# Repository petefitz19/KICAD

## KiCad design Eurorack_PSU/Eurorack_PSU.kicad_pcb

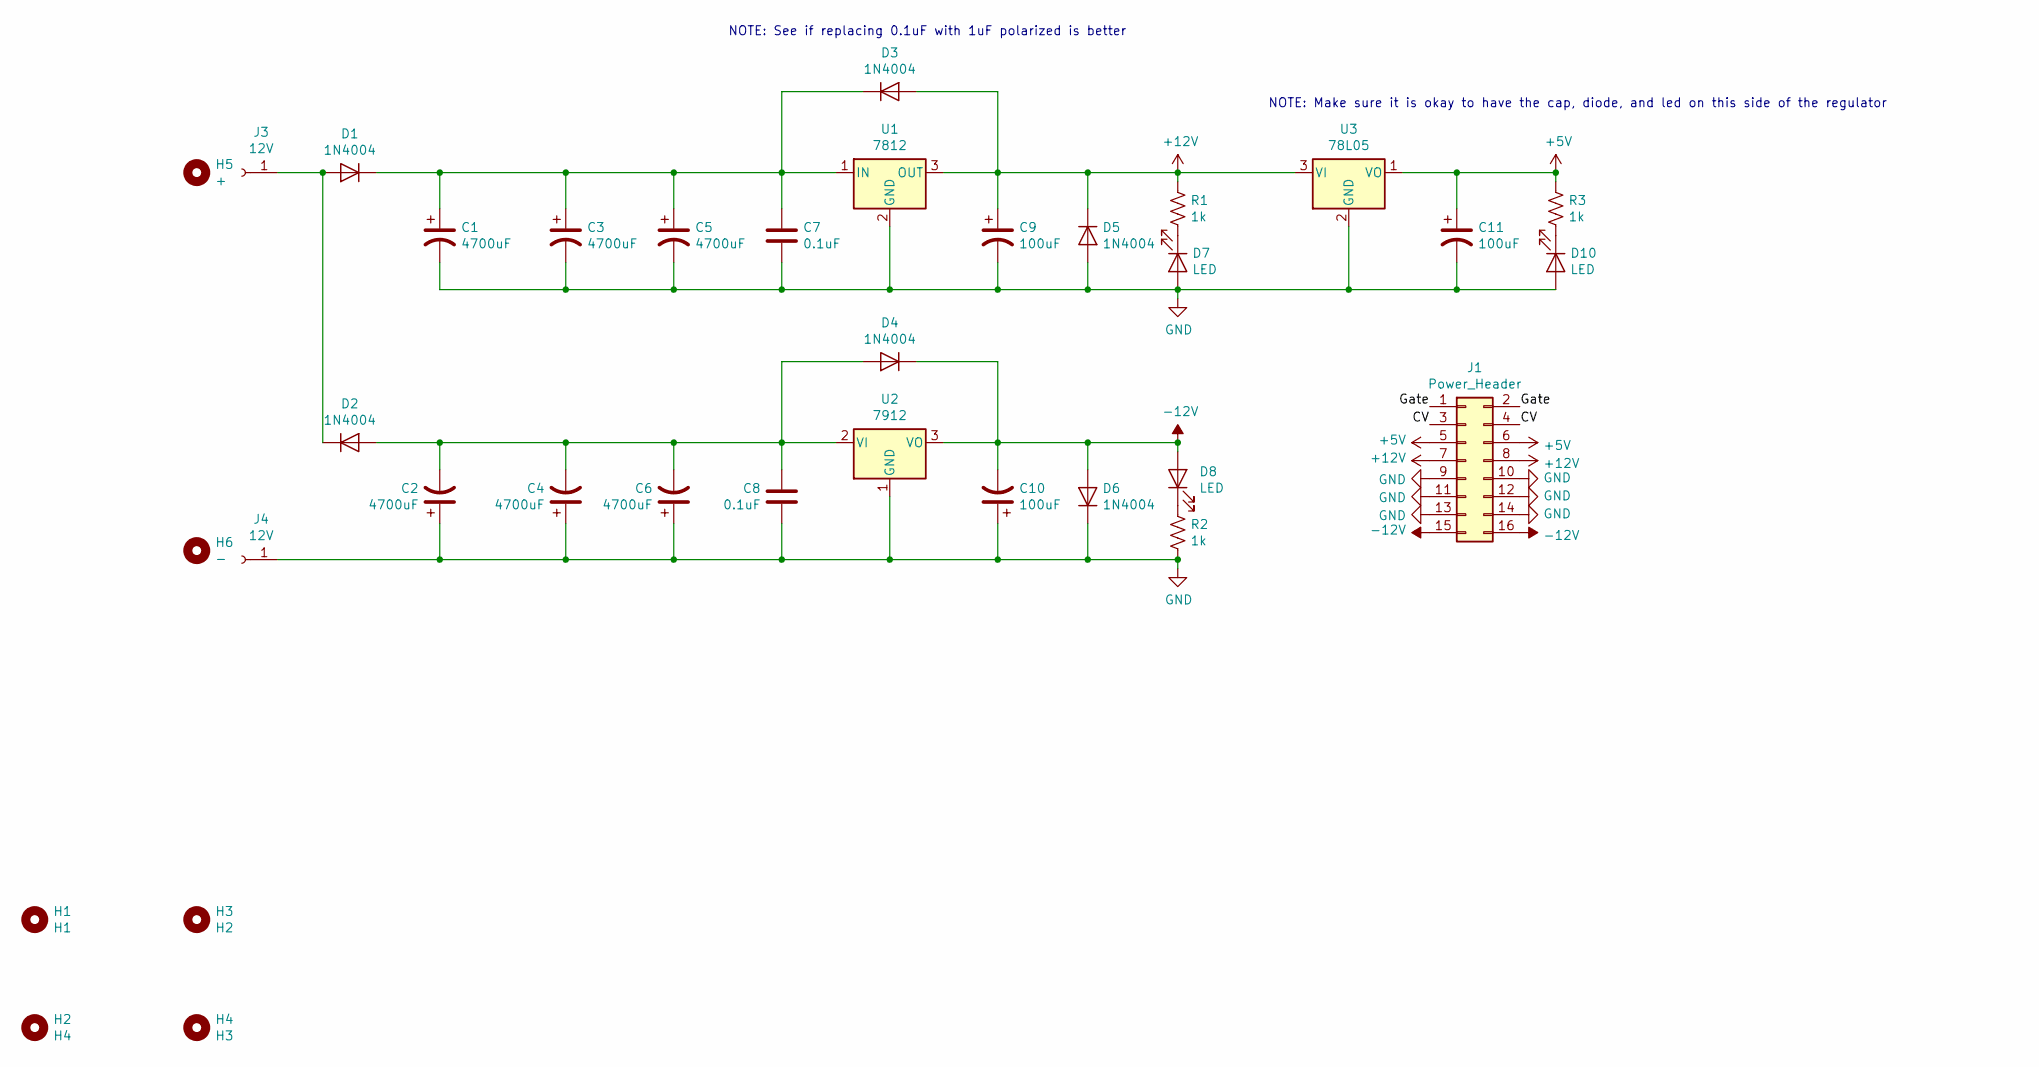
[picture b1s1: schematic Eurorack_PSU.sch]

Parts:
C1, C2, C3, C4, C5, C6: 4700uF; CP_Radial_D16.0mm_P7.50mm
C7, C8: 0.1uF; C_Disc_D5.0mm_W2.5mm_P5.00mm
C9, C10, C11: 100uF; CP_Radial_D6.3mm_P2.50mm
D1, D2, D3, D4, D5, D6: 1N4004; D_DO-35_SOD27_P7.62mm_Horizontal
D7, D8, D10: LED; LED_D3.0mm
H1: H1; MountingHole_3mm
H2: H4; MountingHole_3mm
H3: H2; MountingHole_3mm
H4: H3; MountingHole_3mm
H5: +; MountingHole_2mm
H6: -; MountingHole_2mm
J1: Power_Header; PinSocket_2x08_P2.54mm_Vertical
J3, J4: 12V; PinSocket_1x01_P2.54mm_Vertical
R1, R2, R3: 1k; R_Axial_DIN0207_L6.3mm_D2.5mm_P7.62mm_Horizontal
U1: 7812; TO-126-3_Vertical
U2: 7912; TO-126-3_Vertical
U3: 78L05; TO-92_Inline

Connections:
+5V: C11.1, J1.5, J1.6, R3.1, U3.1 (VO)
+12V: C9.1, D3.2 (A), D5.1 (K), J1.7, J1.8, R1.1, U1.3 (OUT), U3.3 (VI)
-12V: C10.2, D4.1 (K), D6.2 (A), D8.2 (A), J1.15, J1.16, U2.3 (VO)
/CV: J1.3, J1.4
/Gate: J1.1, J1.2
GND: C1.2, C2.1, C3.2, C4.1, C5.2, C6.1, C7.2, C8.1, C9.2, C10.1, C11.2, D5.2 (A), D6.1 (K), D7.2 (A), D10.2 (A), J1.9, J1.10, J1.11, J1.12, J1.13, J1.14, J4.1, R2.2, U1.2 (GND), U2.1 (GND), U3.2 (GND)
unnamed: C1.1, C3.1, C5.1, C7.1, D1.1 (K), D3.1 (K), U1.1 (IN)
unnamed: C2.2, C4.2, C6.2, C8.2, D2.2 (A), D4.2 (A), U2.2 (VI)
unnamed: D1.2 (A), D2.1 (K), J3.1
unnamed: D7.1 (K), R1.2
unnamed: D8.1 (K), R2.1
unnamed: D10.1 (K), R3.2

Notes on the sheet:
NOTE: Make sure it is okay to have the cap, diode, and led on this side of the regulator
NOTE: See if replacing 0.1uF with 1uF polarized is better

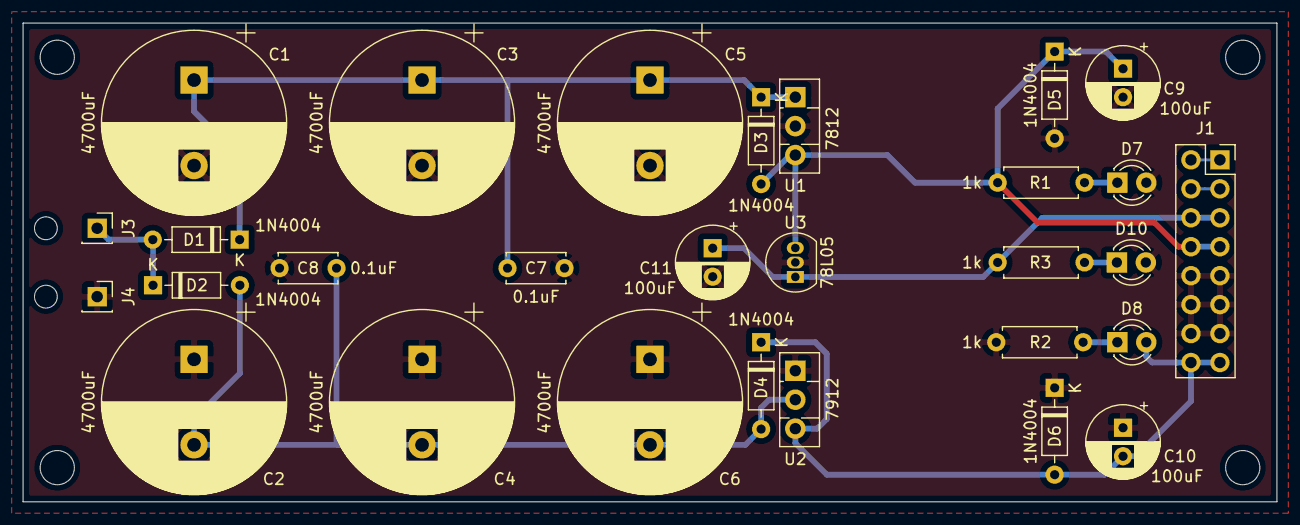
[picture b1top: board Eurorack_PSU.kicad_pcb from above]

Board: 2 copper layers, 110.0 x 42.0 mm, 35 parts (0 on the bottom side), 12 nets.

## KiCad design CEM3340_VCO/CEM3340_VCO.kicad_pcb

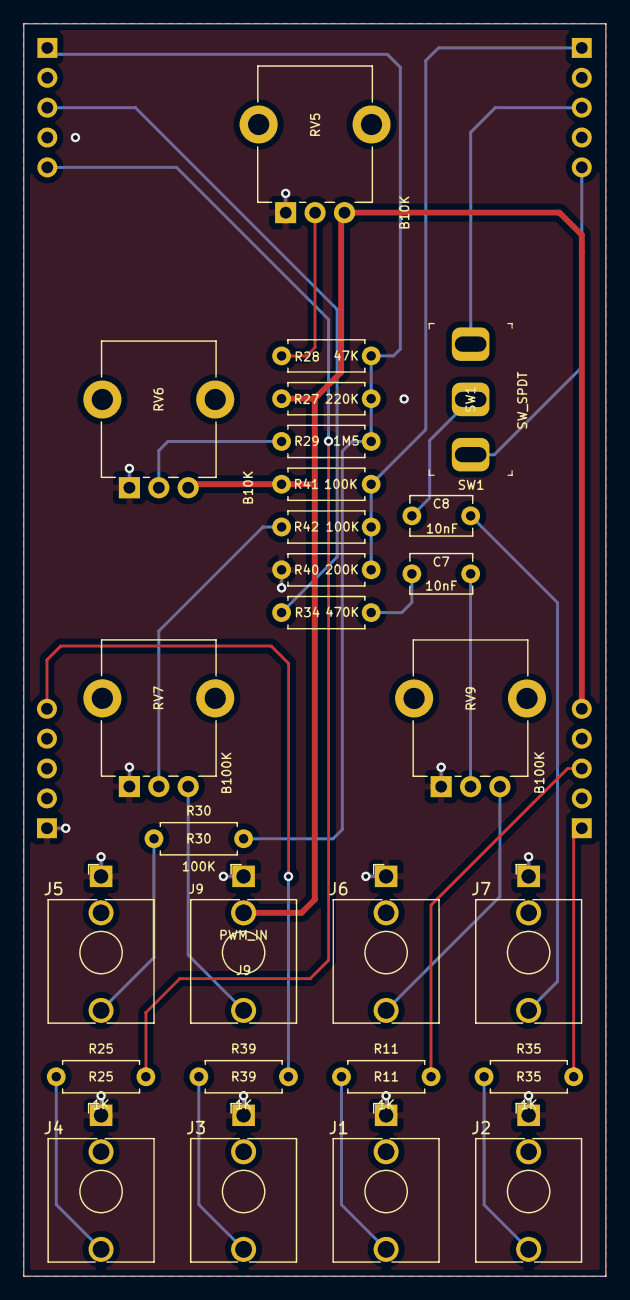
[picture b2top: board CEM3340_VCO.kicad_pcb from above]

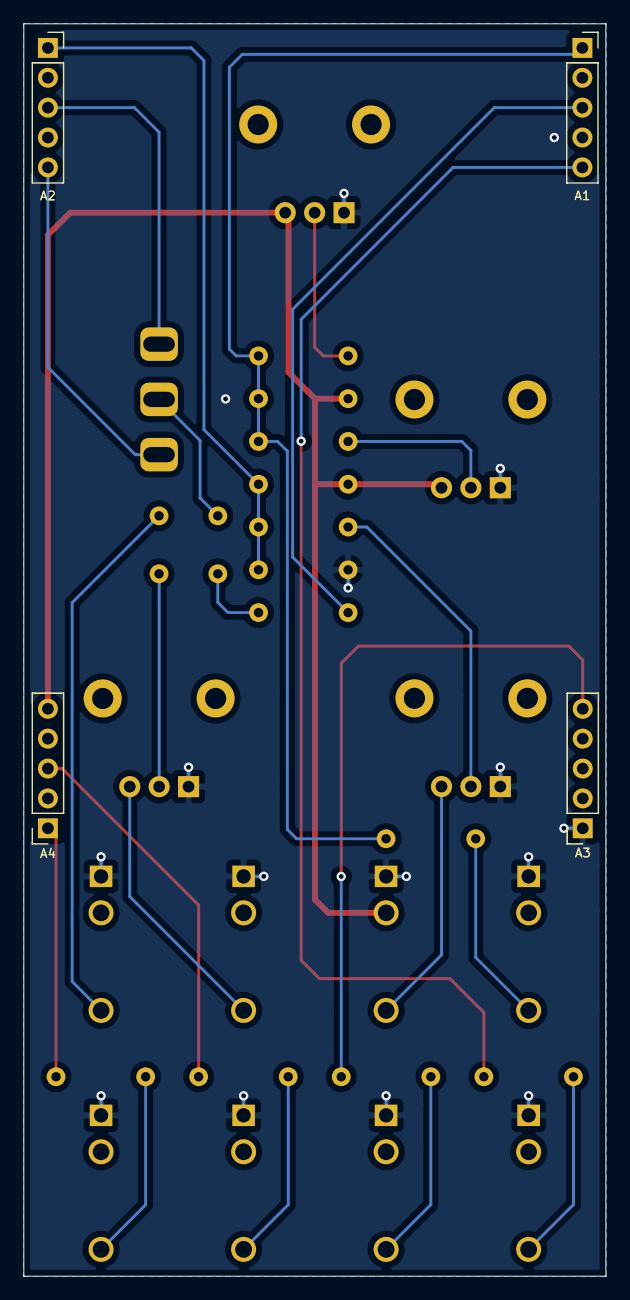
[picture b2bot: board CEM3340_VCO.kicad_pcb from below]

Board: 2 copper layers, 49.5 x 106.5 mm, 31 parts (4 on the bottom side), 25 nets.

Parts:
C7, C8: 10nF; C_Disc_D5.1mm_W3.2mm_P5.00mm
J1: SAW_OUT; Jack_3.5mm_QingPu_WQP-PJ398SM_Vertical_CircularHoles
J2: PULSE_OUT; Jack_3.5mm_QingPu_WQP-PJ398SM_Vertical_CircularHoles
J3: TRI_OUT; Jack_3.5mm_QingPu_WQP-PJ398SM_Vertical_CircularHoles
J4: SIN_OUT; Jack_3.5mm_QingPu_WQP-PJ398SM_Vertical_CircularHoles
J5: V/OCT_IN; Jack_3.5mm_QingPu_WQP-PJ398SM_Vertical_CircularHoles
J6: FM_IN; Jack_3.5mm_QingPu_WQP-PJ398SM_Vertical_CircularHoles
J7: SYNC_IN; Jack_3.5mm_QingPu_WQP-PJ398SM_Vertical_CircularHoles
J9: PWM_IN; Jack_3.5mm_QingPu_WQP-PJ398SM_Vertical_CircularHoles
J10: A1; PinSocket_1x05_P2.54mm_Vertical
J11: A2; PinSocket_1x05_P2.54mm_Vertical
J12: A3; PinSocket_1x05_P2.54mm_Vertical
J13: A4; PinSocket_1x05_P2.54mm_Vertical
R11, R25, R35, R39: 1K; R_Axial_DIN0207_L6.3mm_D2.5mm_P7.62mm_Horizontal
R27: 220K; R_Axial_DIN0207_L6.3mm_D2.5mm_P7.62mm_Horizontal
R28: 47K; R_Axial_DIN0207_L6.3mm_D2.5mm_P7.62mm_Horizontal
R29: 1M5; R_Axial_DIN0207_L6.3mm_D2.5mm_P7.62mm_Horizontal
R30, R41, R42: 100K; R_Axial_DIN0207_L6.3mm_D2.5mm_P7.62mm_Horizontal
R34: 470K; R_Axial_DIN0207_L6.3mm_D2.5mm_P7.62mm_Horizontal
R40: 200K; R_Axial_DIN0207_L6.3mm_D2.5mm_P7.62mm_Horizontal
RV5, RV6: B10K; Potentiometer_Alpha_RD901F-40-00D_Single_Vertical_CircularH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
RV7, RV9: B100K; Potentiometer_Alpha_RD901F-40-00D_Single_Vertical_CircularH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
SW1: SW_SPDT; Toggle_Switch_100SP1T1B4M2QE

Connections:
+5V: J9.TN, J13.5, R27.2, R41.1, RV5.3, RV6.3
/CV_IN_A: J10.1, R27.1, R28.1, R29.1, R30.2
/HSYNC_A: J11.3, SW1.1
/LIN_FM_A: J10.3, R34.1
/PULSE_A: J13.1, R35.2
/PWM_A: J11.1, R40.1, R41.2, R42.2
/SAW_A: J13.3, R11.2
/SIN_A: J10.5, R25.2
/SSYNC_A: J11.5, SW1.3
/TRI_A: J12.5, R39.2
GND: J1.S, J2.S, J3.S, J4.S, J5.S, J6.S, J7.S, J9.S, J12.1, R40.2, RV5.1, RV6.1, RV7.1, RV9.1
unnamed: C7.1, RV9.2
unnamed: C7.2, R34.2
unnamed: C8.1, J7.T
unnamed: C8.2, SW1.2
unnamed: J1.T, R11.1
unnamed: J2.T, R35.1
unnamed: J3.T, R39.1
unnamed: J4.T, R25.1
unnamed: J5.T, R30.1
unnamed: J6.T, RV9.3
unnamed: J9.T, RV7.3
unnamed: R28.2, RV5.2
unnamed: R29.2, RV6.2
unnamed: R42.1, RV7.2

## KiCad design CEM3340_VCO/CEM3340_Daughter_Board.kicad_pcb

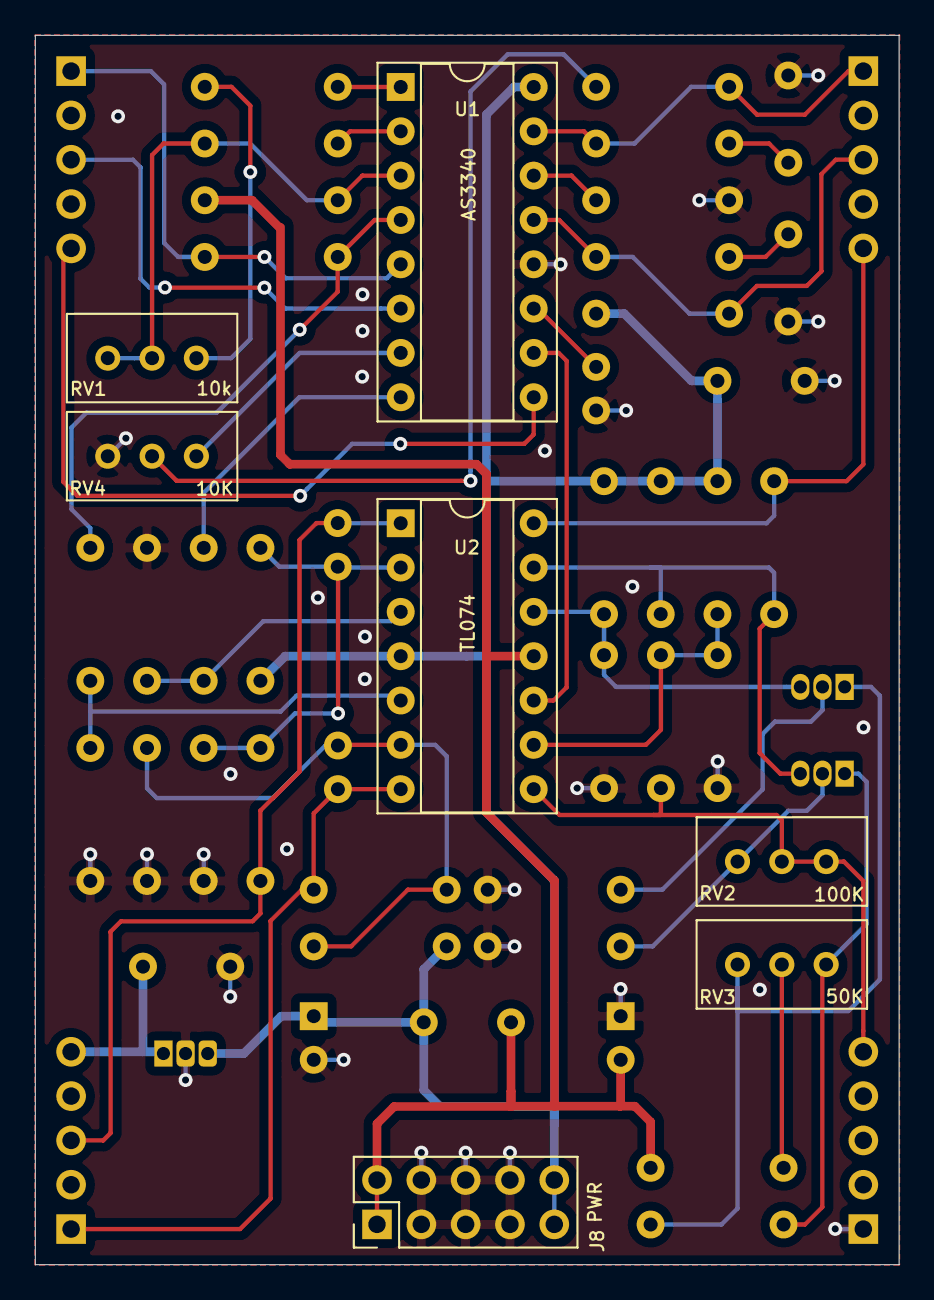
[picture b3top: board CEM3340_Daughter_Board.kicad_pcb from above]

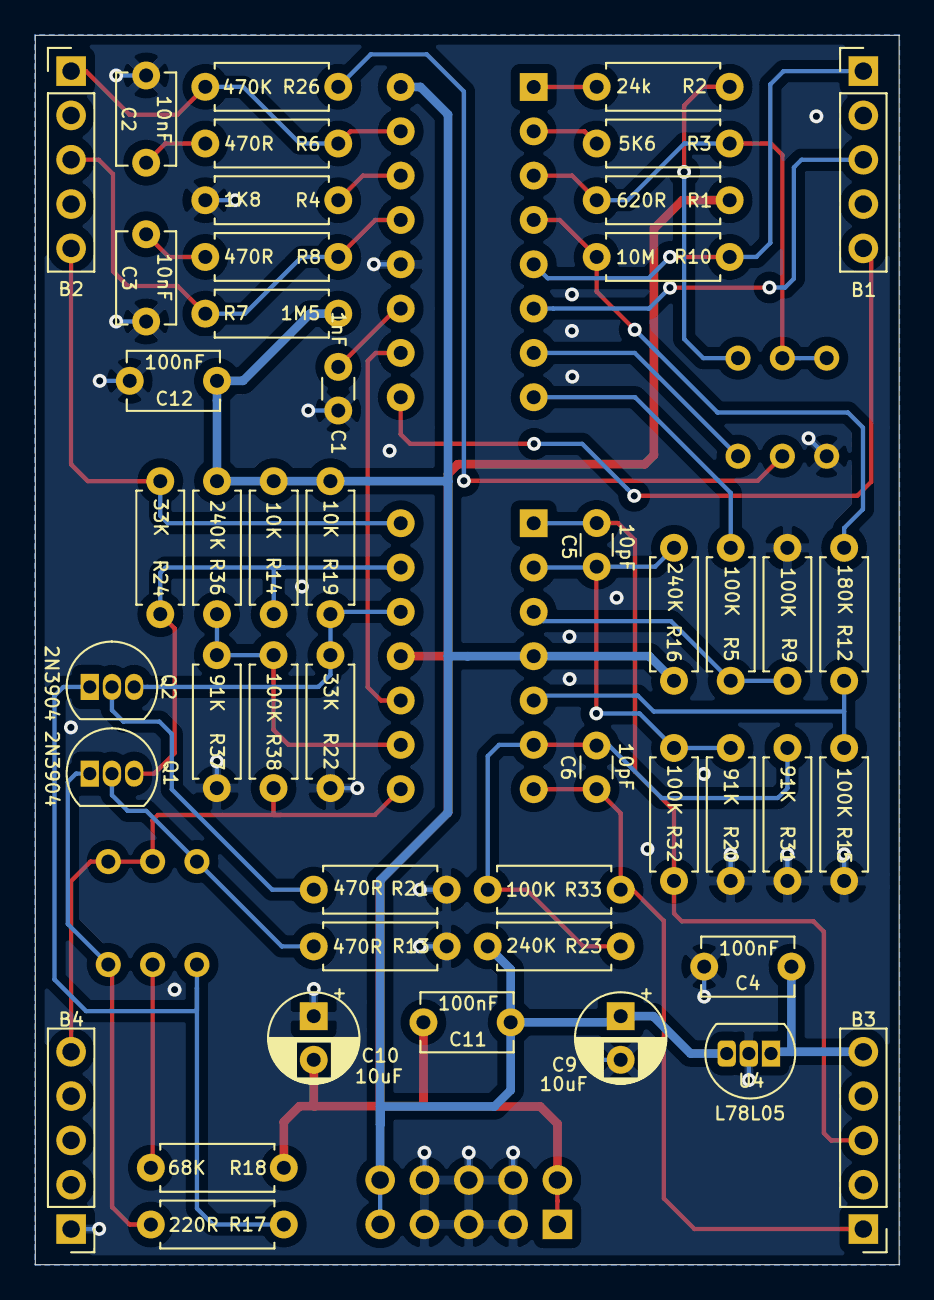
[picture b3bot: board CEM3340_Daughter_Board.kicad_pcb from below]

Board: 2 copper layers, 49.5 x 70.5 mm, 54 parts (47 on the bottom side), 38 nets.

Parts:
C1: 1nF; C_Disc_D3.0mm_W1.6mm_P2.50mm
C2, C3: 10nF; C_Disc_D5.1mm_W3.2mm_P5.00mm
C4, C11, C12: 100nF; C_Disc_D5.1mm_W3.2mm_P5.00mm
C5, C6: 10pF; C_Disc_D3.0mm_W1.6mm_P2.50mm
C9, C10: 10uF; CP_Radial_D5.0mm_P2.50mm
J8: PWR; PinHeader_2x05_P2.54mm_Vertical
J14: B1; PinHeader_1x05_P2.54mm_Vertical
J15: B2; PinHeader_1x05_P2.54mm_Vertical
J16: B3; PinHeader_1x05_P2.54mm_Vertical
J17: B4; PinHeader_1x05_P2.54mm_Vertical
Q1, Q2: 2N3904; TO-92_Inline
R1: 620R; R_Axial_DIN0207_L6.3mm_D2.5mm_P7.62mm_Horizontal
R2: 24k; R_Axial_DIN0207_L6.3mm_D2.5mm_P7.62mm_Horizontal
R3: 5K6; R_Axial_DIN0207_L6.3mm_D2.5mm_P7.62mm_Horizontal
R4: 1K8; R_Axial_DIN0207_L6.3mm_D2.5mm_P7.62mm_Horizontal
R5, R9, R15, R32, R33, R38: 100K; R_Axial_DIN0207_L6.3mm_D2.5mm_P7.62mm_Horizontal
R6, R8, R13, R21: 470R; R_Axial_DIN0207_L6.3mm_D2.5mm_P7.62mm_Horizontal
R7: 1M5; R_Axial_DIN0207_L6.3mm_D2.5mm_P7.62mm_Horizontal
R10: 10M; R_Axial_DIN0207_L6.3mm_D2.5mm_P7.62mm_Horizontal
R12: 180K; R_Axial_DIN0207_L6.3mm_D2.5mm_P7.62mm_Horizontal
R14, R19: 10K; R_Axial_DIN0207_L6.3mm_D2.5mm_P7.62mm_Horizontal
R16, R23, R36: 240K; R_Axial_DIN0207_L6.3mm_D2.5mm_P7.62mm_Horizontal
R17: 220R; R_Axial_DIN0207_L6.3mm_D2.5mm_P7.62mm_Horizontal
R18: 68K; R_Axial_DIN0207_L6.3mm_D2.5mm_P7.62mm_Horizontal
R20, R31, R37: 91K; R_Axial_DIN0207_L6.3mm_D2.5mm_P7.62mm_Horizontal
R22, R24: 33K; R_Axial_DIN0207_L6.3mm_D2.5mm_P7.62mm_Horizontal
R26: 470K; R_Axial_DIN0207_L6.3mm_D2.5mm_P7.62mm_Horizontal
RV1: 10k; Potentiometer_Bourns_3296W_Vertical
RV2: 100K; Potentiometer_Bourns_3296W_Vertical
RV3: 50K; Potentiometer_Bourns_3296W_Vertical
RV4: 10K; Potentiometer_Bourns_3296W_Vertical
U1: AS3340; DIP-16_W7.62mm_Socket
U2: TL074; DIP-14_W7.62mm_Socket
U4: L78L05; TO-92L_Inline

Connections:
+5V: C4.1, J16.5, U4.1
+12V: C9.1, C11.1, C12.2, J8.9, J8.10, R7.2, R14.1, R16.2, R19.1, R23.2, R36.2, U1.16, U2.4, U4.3
-12V: C10.2, C11.2, J8.1, J8.2, R1.2, R18.2, U2.11
/CV_IN: J15.1, R6.2, R26.1, U1.15
/HSYNC_B: J14.3, U1.6
/LIN_FM_B: J15.3, R7.1, R8.1, U1.13
/PULSE: R10.2, R12.2, U1.4
/PULSE_B: C6.1, J16.1, R33.1, U2.7
/PWM_B: J14.1, R10.1, U1.5
/SAW: R5.2, U1.8
/SAW_B: C5.1, J16.3, R32.1, U2.1
/SIN_B: J15.5, R24.1, U2.14
/SIN_SHAPE: J17.5, R38.1, RV2.2, RV2.3, U2.8
/SSYNC_B: J14.5, U1.9
/TRI: U1.10, U2.10
/VHFT: RV4.3, U1.7
GND: C1.1, C2.1, C3.2, C4.2, C9.2, C10.1, C12.1, J8.3, J8.4, J8.5, J8.6, J8.7, J8.8, J17.1, R4.1, R9.2, R13.2, R15.2, R20.2, R21.2, R22.2, R31.2, R37.2, RV4.1, U1.12, U4.2
unnamed: C1.2, U1.11
unnamed: C2.2, R6.1
unnamed: C3.1, R8.2
unnamed: C5.2, R16.1, R20.1, R32.2, U2.2
unnamed: C6.2, R23.1, R31.1, R33.2, U2.6
unnamed: Q1.1, R17.2, RV3.3
unnamed: Q1.2, R13.1, RV2.1
unnamed: Q1.3, R14.2, R24.2, U2.13
unnamed: Q2.1, R17.1, RV3.1
unnamed: Q2.2, R21.1
unnamed: Q2.3, R19.2, R22.1, U2.12
unnamed: R1.1, R3.2, RV1.1, RV1.2, U1.3
unnamed: R2.1, U1.1
unnamed: R2.2, RV1.3
unnamed: R3.1, U1.2
unnamed: R4.2, U1.14
unnamed: R5.1, R9.1, U2.3
unnamed: R12.1, R15.1, U2.5
unnamed: R18.1, RV3.2
unnamed: R26.2, RV4.2
unnamed: R36.1, R37.1, R38.2, U2.9

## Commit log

2020-11-20 Added Eurorack PSU and CEM3340 files
